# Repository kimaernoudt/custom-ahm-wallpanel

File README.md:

# Custom AHM Wallpanel

A DIY wall controller for an Allen & Heath **AHM-16** (cafe install).

## What it does
- **4 knobs with LED rings**, left to right:
  - INPUT: input level of the active scene (IPAD → input 1, DJ → input 3, EXTRA → input 5)
  - TRAP: control group 1
  - SAS: control group 2
  - TOOG: zone 3
- Turn a knob to change the level. Pressing a knob does nothing; a ring turns red if that channel is muted from elsewhere.
- **5 lit buttons**: ON/OFF (amps, through an AHM GPO), IPAD, DJ and EXTRA recall scenes 2–4, BEL plays a sample.
- The panel talks to the AHM over its TCP control protocol (port 51325) and runs on a single PoE network cable.

## Hardware
- Olimex ESP32-POE, an MCP23017 I/O expander, 4 × EC11 encoders, 4 × WS2812 12-LED rings and 5 × LED buttons
- See [PARTS-LIST.md](PARTS-LIST.md) (about €47 with an Olimex you already own) and [wiring/WIRING.md](wiring/WIRING.md)

Or skip the hand wiring: [`pcb/`](pcb/) has a ready-to-order panel PCB (KiCad 7, gerbers + JLCPCB assembly files) that carries the encoders, buttons, all LEDs and the MCP23017, and connects to the Olimex with one UEXT cable.

## Enclosure
3D-printable, 170 × 90 mm faceplate on a 35 mm deep surface-mount back box with keyholes for wall screws. See [`3d/`](3d/):
- `faceplate.stl`: print it face-down
- `backbox.stl`
- `labels.stl` (optional): white inlay for multi-material printers
- `faceplate-pcb.stl` + `buttoncap.stl`: the faceplate and translucent button caps for the panel PCB
- `ahm-panel.scad`: parametric source. Export a part with `openscad -D 'part="faceplate"' -o faceplate.stl ahm-panel.scad`

The 2D laser-cut file is in `design/faceplate-cut.svg` (1:1 mm, red = cut, blue = engrave).

## Firmware
- `firmware/ahm_test/`: first connection test with 1 encoder (GPIO32/33) and 1 button (GPIO4). Set your AHM's IP address at the top, then build with the board "OLIMEX ESP32-PoE".
- `firmware/promicro_encoder_test/`: one encoder on a Pro Micro over USB, via `tools/serial_bridge.py`.
- `firmware/ahm_panel/`: **the full panel firmware**, set up per room from a web page. See its [README](firmware/ahm_panel/README.md).

## Test without hardware
[`tools/`](tools/) has a virtual panel for your computer and a fake AHM that prints every command it receives,
so you can check the protocol against System Manager, the real AHM, or nothing at all. See [tools/README.md](tools/README.md).

## Docs
- [docs/ahm-protocol-and-config.md](docs/ahm-protocol-and-config.md): AHM TCP commands and a summary of the cafe show file

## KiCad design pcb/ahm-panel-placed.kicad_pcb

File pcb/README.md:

# Panel PCB (v2, untested)

v2 (2026-11-09) follows the final faceplate layout: 5 buttons ON/OFF, IPAD, DJ, EXTRA and BEL (v1 had 4 buttons under the knobs).

One board that replaces the hand wiring: the 4 encoders, the 5 buttons, all 48 ring LEDs, 5 button LEDs and the
MCP23017 sit on it. One 10-wire UEXT cable and one 2-wire 5 V cable go to the Olimex ESP32-POE.

## Fit

- Board 162 x 82 mm with 11 mm corner notches, so it clears the back box walls (1.6 mm) and the screw bosses (1 mm).
- It hangs from the 4 encoder nuts: the PCB front sits 6.5 mm behind the faceplate (the EC11E body height).
  Nothing on the front is taller than the 5 mm tact switches.
- Behind the board there are ~27 mm left for the Olimex and the cables (35 mm box).
- Faceplate for this board: `openscad -D PCB=true -D 'part="faceplate"' 3d/ahm-panel.scad` (`3d/faceplate-pcb.stl`).
  It has light tubes round each LED window so the LEDs don't bleed into each other, and no ring pockets.
- Button caps: `3d/buttoncap.stl`, print 4 in clear/natural PETG. They sit on the switches, flange behind the faceplate,
  and a WS2812B (the same 5050 LED as the rings) under each flange lights the cap.

## Connections

| J1 UEXT (2x5, back) | Olimex | Use |
|---|---|---|
| 1 | 3.3 V | MCP23017, pull-ups |
| 2 | GND | |
| 3 | GPIO4 | LED data (shifted to 5 V on the board) |
| 4 | GPIO36 | ON/OFF, IPAD, DJ, EXTRA (resistor ladder 0 / 3.3k / 8.2k / 22k; the pull-up is the Olimex's own 10k behind its diode D4) |
| 5 | GPIO16 | I2C SCL (pull-ups 2.2k on the Olimex) |
| 6 | GPIO13 | I2C SDA |

J2 (JST XH, back): 5 V and GND for the LEDs, from the Olimex 5 V pin. The UEXT pin-out was checked against the Olimex
ESP32-POE Rev L schematic.

Firmware: build with `PANEL_PCB 1` (top of `firmware/ahm_panel/panel_io.h`). That moves the ladder to GPIO36 and drives
the button LEDs as pixels 48-52 of the LED chain (BEL, EXTRA, DJ, IPAD, ON/OFF). BEL is on MCP23017 GPB5 (pin 6), active low with
the MCP pull-up.

## Ordering (JLCPCB)

Step-by-step order checklist and the parts to buy separately: [ORDERING.md](ORDERING.md).

- `production/ahm-panel-gerbers.zip`: 2 layers, 1.6 mm, any colour.
- Assembly, top side, Standard PCBA: `production/ahm-panel-bom.csv` + `production/ahm-panel-cpl-jlc.csv`.
  JLCPCB fits everything on the front: the SMD parts, all 53 WS2812B-V5 LEDs (C2874885), the 4 smooth (no-click) ALPS EC11E1834403
  encoders (C361165) and the 4 tact switches (C393938). The last two are through-hole, so JLC hand-solders them.
- `ahm-panel-cpl-jlc.csv` gives the encoders and switches at their body centre (KiCad places them by pin 1).
- Solder yourself: J1 and J2 on the back (`production/hand-solder.csv`).

## Rebuild

```
python3 place.py                      # parts + netlist -> ahm-panel-placed.kicad_pcb, parts.csv
python3 route.py freerouting-2.1.0.jar   # autoroute, GND pours, DRC -> ahm-panel.kicad_pcb, drc.rpt
./export.sh                           # gerbers, drill, placement, BOM -> production/
```

KiCad 7. DRC: 0 unconnected, no copper errors. The remaining warnings are the ring LED courtyards touching (the
pads themselves pass the 0.2 mm clearance check) and library-table notices.

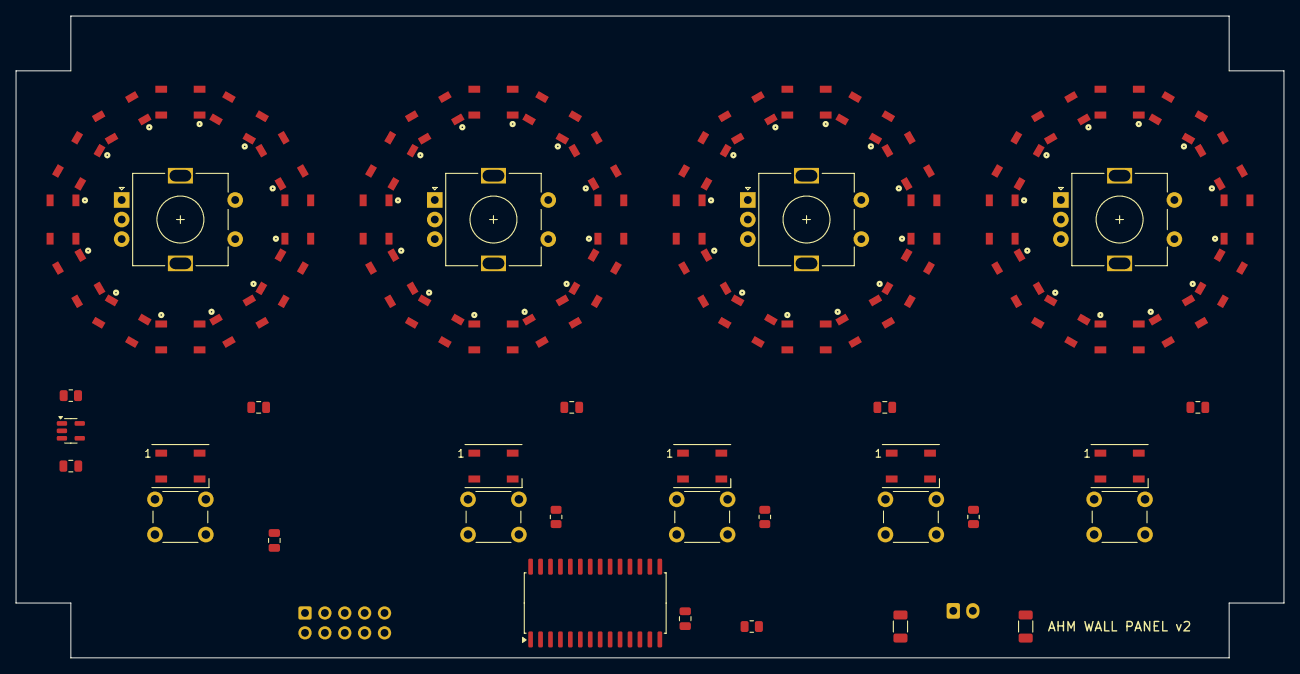
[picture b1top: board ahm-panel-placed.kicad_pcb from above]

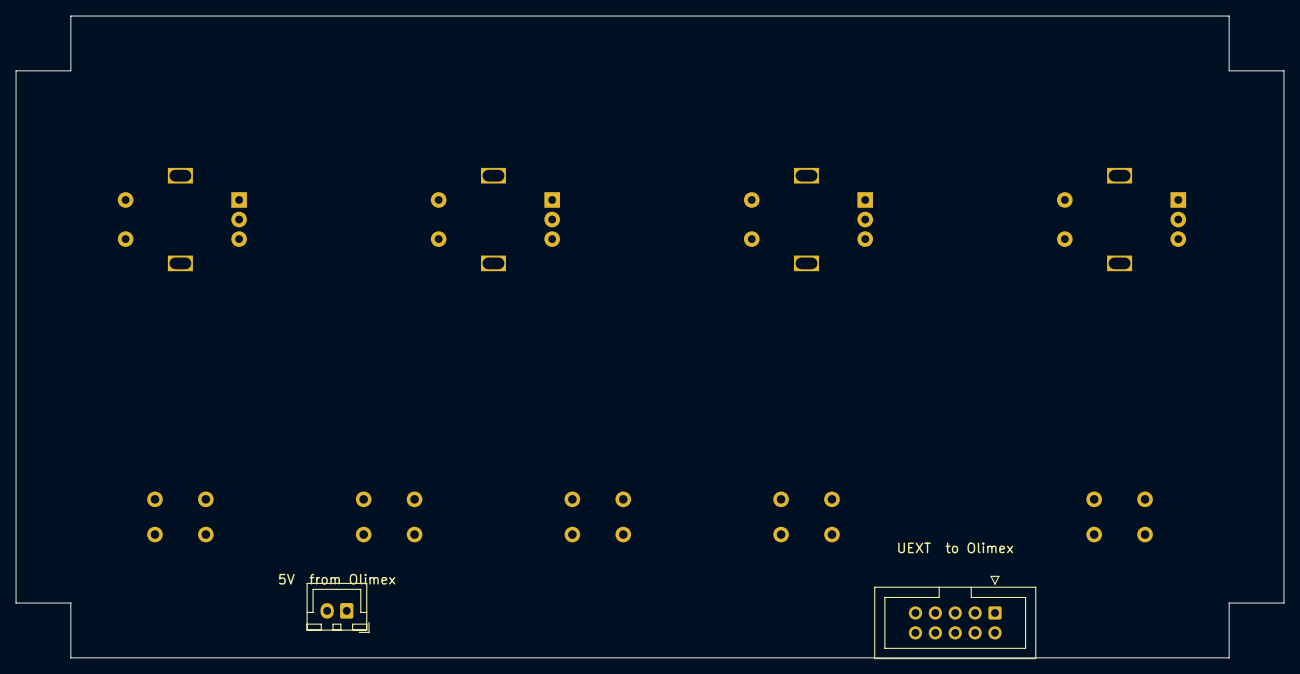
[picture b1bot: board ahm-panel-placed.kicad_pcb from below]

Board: 2 copper layers, 162.0 x 82.0 mm, 80 parts (2 on the bottom side), 78 nets, no tracks yet.

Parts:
C1, C2, C9: 100nF; C_0805_2012Metric
C3, C4: 22uF; C_1206_3216Metric
C5, C6, C7, C8: 10uF; C_0805_2012Metric
ENC1, ENC2, ENC3, ENC4: EC11E with switch, 20 mm shaft; RotaryEncoder_Alps_EC11E-Switch_Vertical_H20mm
J1: UEXT 2x5 box header; IDC-Header_2x05_P2.54mm_Vertical
J2: JST XH 2-pin; JST_XH_B2B-XH-A_1x02_P2.50mm_Vertical
LED1, LED2, LED3, LED4, LED5, LED6, LED7, LED8, LED9, LED10, LED11, LED12, LED13, LED14, LED15, LED16, LED17, LED18, LED19, LED20, LED21, LED22, LED23, LED24, LED25, LED26, LED27, LED28, LED29, LED30, LED31, LED32, LED33, LED34, LED35, LED36, LED37, LED38, LED39, LED40, LED41, LED42, LED43, LED44, LED45, LED46, LED47, LED48, LED49, LED50, LED51, LED52, LED53: WS2812B-B; LED_WS2812B_PLCC4_5.0x5.0mm_P3.2mm
R2: 3.3k; R_0805_2012Metric
R3: 8.2k; R_0805_2012Metric
R4: 22k; R_0805_2012Metric
R5: 10k; R_0805_2012Metric
R8: 33R; R_0805_2012Metric
SW1, SW2, SW3, SW4, SW5: 6x6 mm tact, 5 mm high; SW_PUSH_6mm_H5mm
U1: MCP23017-E/SO; SOIC-28W_7.5x17.9mm_P1.27mm
U2: 74AHCT1G125; SOT-23-5

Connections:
+3V3: C2.1, J1.1, R5.1, U1.9
+5V: C3.1, C4.1, C5.1, C6.1, C7.1, C8.1, C9.1, J2.1, LED1.1, LED2.1, LED3.1, LED4.1, LED5.1, LED6.1, LED7.1, LED8.1, LED9.1, LED10.1, LED11.1, LED12.1, LED13.1, LED14.1, LED15.1, LED16.1, LED17.1, LED18.1, LED19.1, LED20.1, LED21.1, LED22.1, LED23.1, LED24.1, LED25.1, LED26.1, LED27.1, LED28.1, LED29.1, LED30.1, LED31.1, LED32.1, LED33.1, LED34.1, LED35.1, LED36.1, LED37.1, LED38.1, LED39.1, LED40.1, LED41.1, LED42.1, LED43.1, LED44.1, LED45.1, LED46.1, LED47.1, LED48.1, LED49.1, LED50.1, LED51.1, LED52.1, LED53.1, U2.5
BEL: SW5.1, U1.6
D1: LED1.2, LED2.4
D2: LED2.2, LED3.4
D3: LED3.2, LED4.4
D4: LED4.2, LED5.4
D5: LED5.2, LED6.4
D6: LED6.2, LED7.4
D7: LED7.2, LED8.4
D8: LED8.2, LED9.4
D9: LED9.2, LED10.4
D10: LED10.2, LED11.4
D11: LED11.2, LED12.4
D12: LED12.2, LED13.4
D13: LED13.2, LED14.4
D14: LED14.2, LED15.4
D15: LED15.2, LED16.4
D16: LED16.2, LED17.4
D17: LED17.2, LED18.4
D18: LED18.2, LED19.4
D19: LED19.2, LED20.4
D20: LED20.2, LED21.4
D21: LED21.2, LED22.4
D22: LED22.2, LED23.4
D23: LED23.2, LED24.4
D24: LED24.2, LED25.4
D25: LED25.2, LED26.4
D26: LED26.2, LED27.4
D27: LED27.2, LED28.4
D28: LED28.2, LED29.4
D29: LED29.2, LED30.4
D30: LED30.2, LED31.4
D31: LED31.2, LED32.4
D32: LED32.2, LED33.4
D33: LED33.2, LED34.4
D34: LED34.2, LED35.4
D35: LED35.2, LED36.4
D36: LED36.2, LED37.4
D37: LED37.2, LED38.4
D38: LED38.2, LED39.4
D39: LED39.2, LED40.4
D40: LED40.2, LED41.4
D41: LED41.2, LED42.4
D42: LED42.2, LED43.4
D43: LED43.2, LED44.4
D44: LED44.2, LED45.4
D45: LED45.2, LED46.4
D46: LED46.2, LED47.4
D47: LED47.2, LED48.4
D48: LED48.2, LED49.4
D49: LED49.2, LED50.4
D50: LED50.2, LED51.4
D51: LED51.2, LED52.4
D52: LED52.2, LED53.4
ENC1_A: ENC1.A, U1.21
ENC1_B: ENC1.B, U1.22
ENC1_SW: ENC1.S1, U1.27
ENC2_A: ENC2.A, U1.23
ENC2_B: ENC2.B, U1.24
ENC2_SW: ENC2.S1, U1.3
ENC3_A: ENC3.A, U1.25
ENC3_B: ENC3.B, U1.26
ENC3_SW: ENC3.S1, U1.4
ENC4_A: ENC4.A, U1.1
ENC4_B: ENC4.B, U1.2
ENC4_SW: ENC4.S1, U1.5
GND: C1.2, C2.2, C3.2, C4.2, C5.2, C6.2, C7.2, C8.2, C9.2, ENC1.C, ENC1.MP, ENC1.S2, ENC2.C, ENC2.MP, ENC2.S2, ENC3.C, ENC3.MP, ENC3.S2, ENC4.C, ENC4.MP, ENC4.S2, J1.2, J2.2, LED1.3, LED2.3, LED3.3, LED4.3, LED5.3, LED6.3, LED7.3, LED8.3, LED9.3, LED10.3, LED11.3, LED12.3, LED13.3, LED14.3, LED15.3, LED16.3, LED17.3, LED18.3, LED19.3, LED20.3, LED21.3, LED22.3, LED23.3, LED24.3, LED25.3, LED26.3, LED27.3, LED28.3, LED29.3, LED30.3, LED31.3, LED32.3, LED33.3, LED34.3, LED35.3, LED36.3, LED37.3, LED38.3, LED39.3, LED40.3, LED41.3, LED42.3, LED43.3, LED44.3, LED45.3, LED46.3, LED47.3, LED48.3, LED49.3, LED50.3, LED51.3, LED52.3, LED53.3, SW1.2, SW2.2, SW3.2, SW4.2, SW5.2, U1.10, U1.15, U1.16, U1.17, U2.1, U2.3
LAD2: R2.2, SW2.1
LAD3: R3.2, SW3.1
LAD4: R4.2, SW4.1
LADDER: C1.1, J1.4, R2.1, R3.1, R4.1, SW1.1
LED_3V3: J1.3, U2.2
LED_5V: R8.1, U2.4
LED_DATA: LED1.4, R8.2
RST: R5.2, U1.18
SCL: J1.5, U1.12
SDA: J1.6, U1.13

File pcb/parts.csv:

ref,value,footprint,lcsc,side
ENC1,"EC11E with switch, 20 mm shaft",RotaryEncoder_Alps_EC11E-Switch_Vertical_H20mm,,top
ENC2,"EC11E with switch, 20 mm shaft",RotaryEncoder_Alps_EC11E-Switch_Vertical_H20mm,,top
ENC3,"EC11E with switch, 20 mm shaft",RotaryEncoder_Alps_EC11E-Switch_Vertical_H20mm,,top
ENC4,"EC11E with switch, 20 mm shaft",RotaryEncoder_Alps_EC11E-Switch_Vertical_H20mm,,top
LED1,WS2812B-B,LED_WS2812B_PLCC4_5.0x5.0mm_P3.2mm,,top
LED2,WS2812B-B,LED_WS2812B_PLCC4_5.0x5.0mm_P3.2mm,,top
LED3,WS2812B-B,LED_WS2812B_PLCC4_5.0x5.0mm_P3.2mm,,top
LED4,WS2812B-B,LED_WS2812B_PLCC4_5.0x5.0mm_P3.2mm,,top
LED5,WS2812B-B,LED_WS2812B_PLCC4_5.0x5.0mm_P3.2mm,,top
LED6,WS2812B-B,LED_WS2812B_PLCC4_5.0x5.0mm_P3.2mm,,top
LED7,WS2812B-B,LED_WS2812B_PLCC4_5.0x5.0mm_P3.2mm,,top
LED8,WS2812B-B,LED_WS2812B_PLCC4_5.0x5.0mm_P3.2mm,,top
LED9,WS2812B-B,LED_WS2812B_PLCC4_5.0x5.0mm_P3.2mm,,top
LED10,WS2812B-B,LED_WS2812B_PLCC4_5.0x5.0mm_P3.2mm,,top
LED11,WS2812B-B,LED_WS2812B_PLCC4_5.0x5.0mm_P3.2mm,,top
LED12,WS2812B-B,LED_WS2812B_PLCC4_5.0x5.0mm_P3.2mm,,top
LED13,WS2812B-B,LED_WS2812B_PLCC4_5.0x5.0mm_P3.2mm,,top
LED14,WS2812B-B,LED_WS2812B_PLCC4_5.0x5.0mm_P3.2mm,,top
LED15,WS2812B-B,LED_WS2812B_PLCC4_5.0x5.0mm_P3.2mm,,top
LED16,WS2812B-B,LED_WS2812B_PLCC4_5.0x5.0mm_P3.2mm,,top
LED17,WS2812B-B,LED_WS2812B_PLCC4_5.0x5.0mm_P3.2mm,,top
LED18,WS2812B-B,LED_WS2812B_PLCC4_5.0x5.0mm_P3.2mm,,top
LED19,WS2812B-B,LED_WS2812B_PLCC4_5.0x5.0mm_P3.2mm,,top
LED20,WS2812B-B,LED_WS2812B_PLCC4_5.0x5.0mm_P3.2mm,,top
LED21,WS2812B-B,LED_WS2812B_PLCC4_5.0x5.0mm_P3.2mm,,top
LED22,WS2812B-B,LED_WS2812B_PLCC4_5.0x5.0mm_P3.2mm,,top
LED23,WS2812B-B,LED_WS2812B_PLCC4_5.0x5.0mm_P3.2mm,,top
LED24,WS2812B-B,LED_WS2812B_PLCC4_5.0x5.0mm_P3.2mm,,top
LED25,WS2812B-B,LED_WS2812B_PLCC4_5.0x5.0mm_P3.2mm,,top
LED26,WS2812B-B,LED_WS2812B_PLCC4_5.0x5.0mm_P3.2mm,,top
LED27,WS2812B-B,LED_WS2812B_PLCC4_5.0x5.0mm_P3.2mm,,top
LED28,WS2812B-B,LED_WS2812B_PLCC4_5.0x5.0mm_P3.2mm,,top
LED29,WS2812B-B,LED_WS2812B_PLCC4_5.0x5.0mm_P3.2mm,,top
LED30,WS2812B-B,LED_WS2812B_PLCC4_5.0x5.0mm_P3.2mm,,top
LED31,WS2812B-B,LED_WS2812B_PLCC4_5.0x5.0mm_P3.2mm,,top
LED32,WS2812B-B,LED_WS2812B_PLCC4_5.0x5.0mm_P3.2mm,,top
LED33,WS2812B-B,LED_WS2812B_PLCC4_5.0x5.0mm_P3.2mm,,top
LED34,WS2812B-B,LED_WS2812B_PLCC4_5.0x5.0mm_P3.2mm,,top
LED35,WS2812B-B,LED_WS2812B_PLCC4_5.0x5.0mm_P3.2mm,,top
LED36,WS2812B-B,LED_WS2812B_PLCC4_5.0x5.0mm_P3.2mm,,top
LED37,WS2812B-B,LED_WS2812B_PLCC4_5.0x5.0mm_P3.2mm,,top
LED38,WS2812B-B,LED_WS2812B_PLCC4_5.0x5.0mm_P3.2mm,,top
LED39,WS2812B-B,LED_WS2812B_PLCC4_5.0x5.0mm_P3.2mm,,top
LED40,WS2812B-B,LED_WS2812B_PLCC4_5.0x5.0mm_P3.2mm,,top
LED41,WS2812B-B,LED_WS2812B_PLCC4_5.0x5.0mm_P3.2mm,,top
LED42,WS2812B-B,LED_WS2812B_PLCC4_5.0x5.0mm_P3.2mm,,top
LED43,WS2812B-B,LED_WS2812B_PLCC4_5.0x5.0mm_P3.2mm,,top
LED44,WS2812B-B,LED_WS2812B_PLCC4_5.0x5.0mm_P3.2mm,,top
LED45,WS2812B-B,LED_WS2812B_PLCC4_5.0x5.0mm_P3.2mm,,top
LED46,WS2812B-B,LED_WS2812B_PLCC4_5.0x5.0mm_P3.2mm,,top
LED47,WS2812B-B,LED_WS2812B_PLCC4_5.0x5.0mm_P3.2mm,,top
LED48,WS2812B-B,LED_WS2812B_PLCC4_5.0x5.0mm_P3.2mm,,top
LED49,WS2812B-B,LED_WS2812B_PLCC4_5.0x5.0mm_P3.2mm,,top
LED50,WS2812B-B,LED_WS2812B_PLCC4_5.0x5.0mm_P3.2mm,,top
LED51,WS2812B-B,LED_WS2812B_PLCC4_5.0x5.0mm_P3.2mm,,top
LED52,WS2812B-B,LED_WS2812B_PLCC4_5.0x5.0mm_P3.2mm,,top
LED53,WS2812B-B,LED_WS2812B_PLCC4_5.0x5.0mm_P3.2mm,,top
SW1,"6x6 mm tact, 5 mm high",SW_PUSH_6mm_H5mm,,top
SW2,"6x6 mm tact, 5 mm high",SW_PUSH_6mm_H5mm,,top
R2,3.3k,R_0805_2012Metric,,top
SW3,"6x6 mm tact, 5 mm high",SW_PUSH_6mm_H5mm,,top
R3,8.2k,R_0805_2012Metric,,top
SW4,"6x6 mm tact, 5 mm high",SW_PUSH_6mm_H5mm,,top
R4,22k,R_0805_2012Metric,,top
SW5,"6x6 mm tact, 5 mm high",SW_PUSH_6mm_H5mm,,top
C1,100nF,C_0805_2012Metric,,top
U1,MCP23017-E/SO,SOIC-28W_7.5x17.9mm_P1.27mm,C47023,top
C2,100nF,C_0805_2012Metric,,top
R5,10k,R_0805_2012Metric,,top
J1,UEXT 2x5 box header,IDC-Header_2x05_P2.54mm_Vertical,,bottom
J2,JST XH 2-pin,JST_XH_B2B-XH-A_1x02_P2.50mm_Vertical,,bottom
C3,22uF,C_1206_3216Metric,,top
C4,22uF,C_1206_3216Metric,,top
C5,10uF,C_0805_2012Metric,,top
C6,10uF,C_0805_2012Metric,,top
C7,10uF,C_0805_2012Metric,,top
C8,10uF,C_0805_2012Metric,,top
U2,74AHCT1G125,SOT-23-5,C7484,top
C9,100nF,C_0805_2012Metric,,top
R8,33R,R_0805_2012Metric,,top
